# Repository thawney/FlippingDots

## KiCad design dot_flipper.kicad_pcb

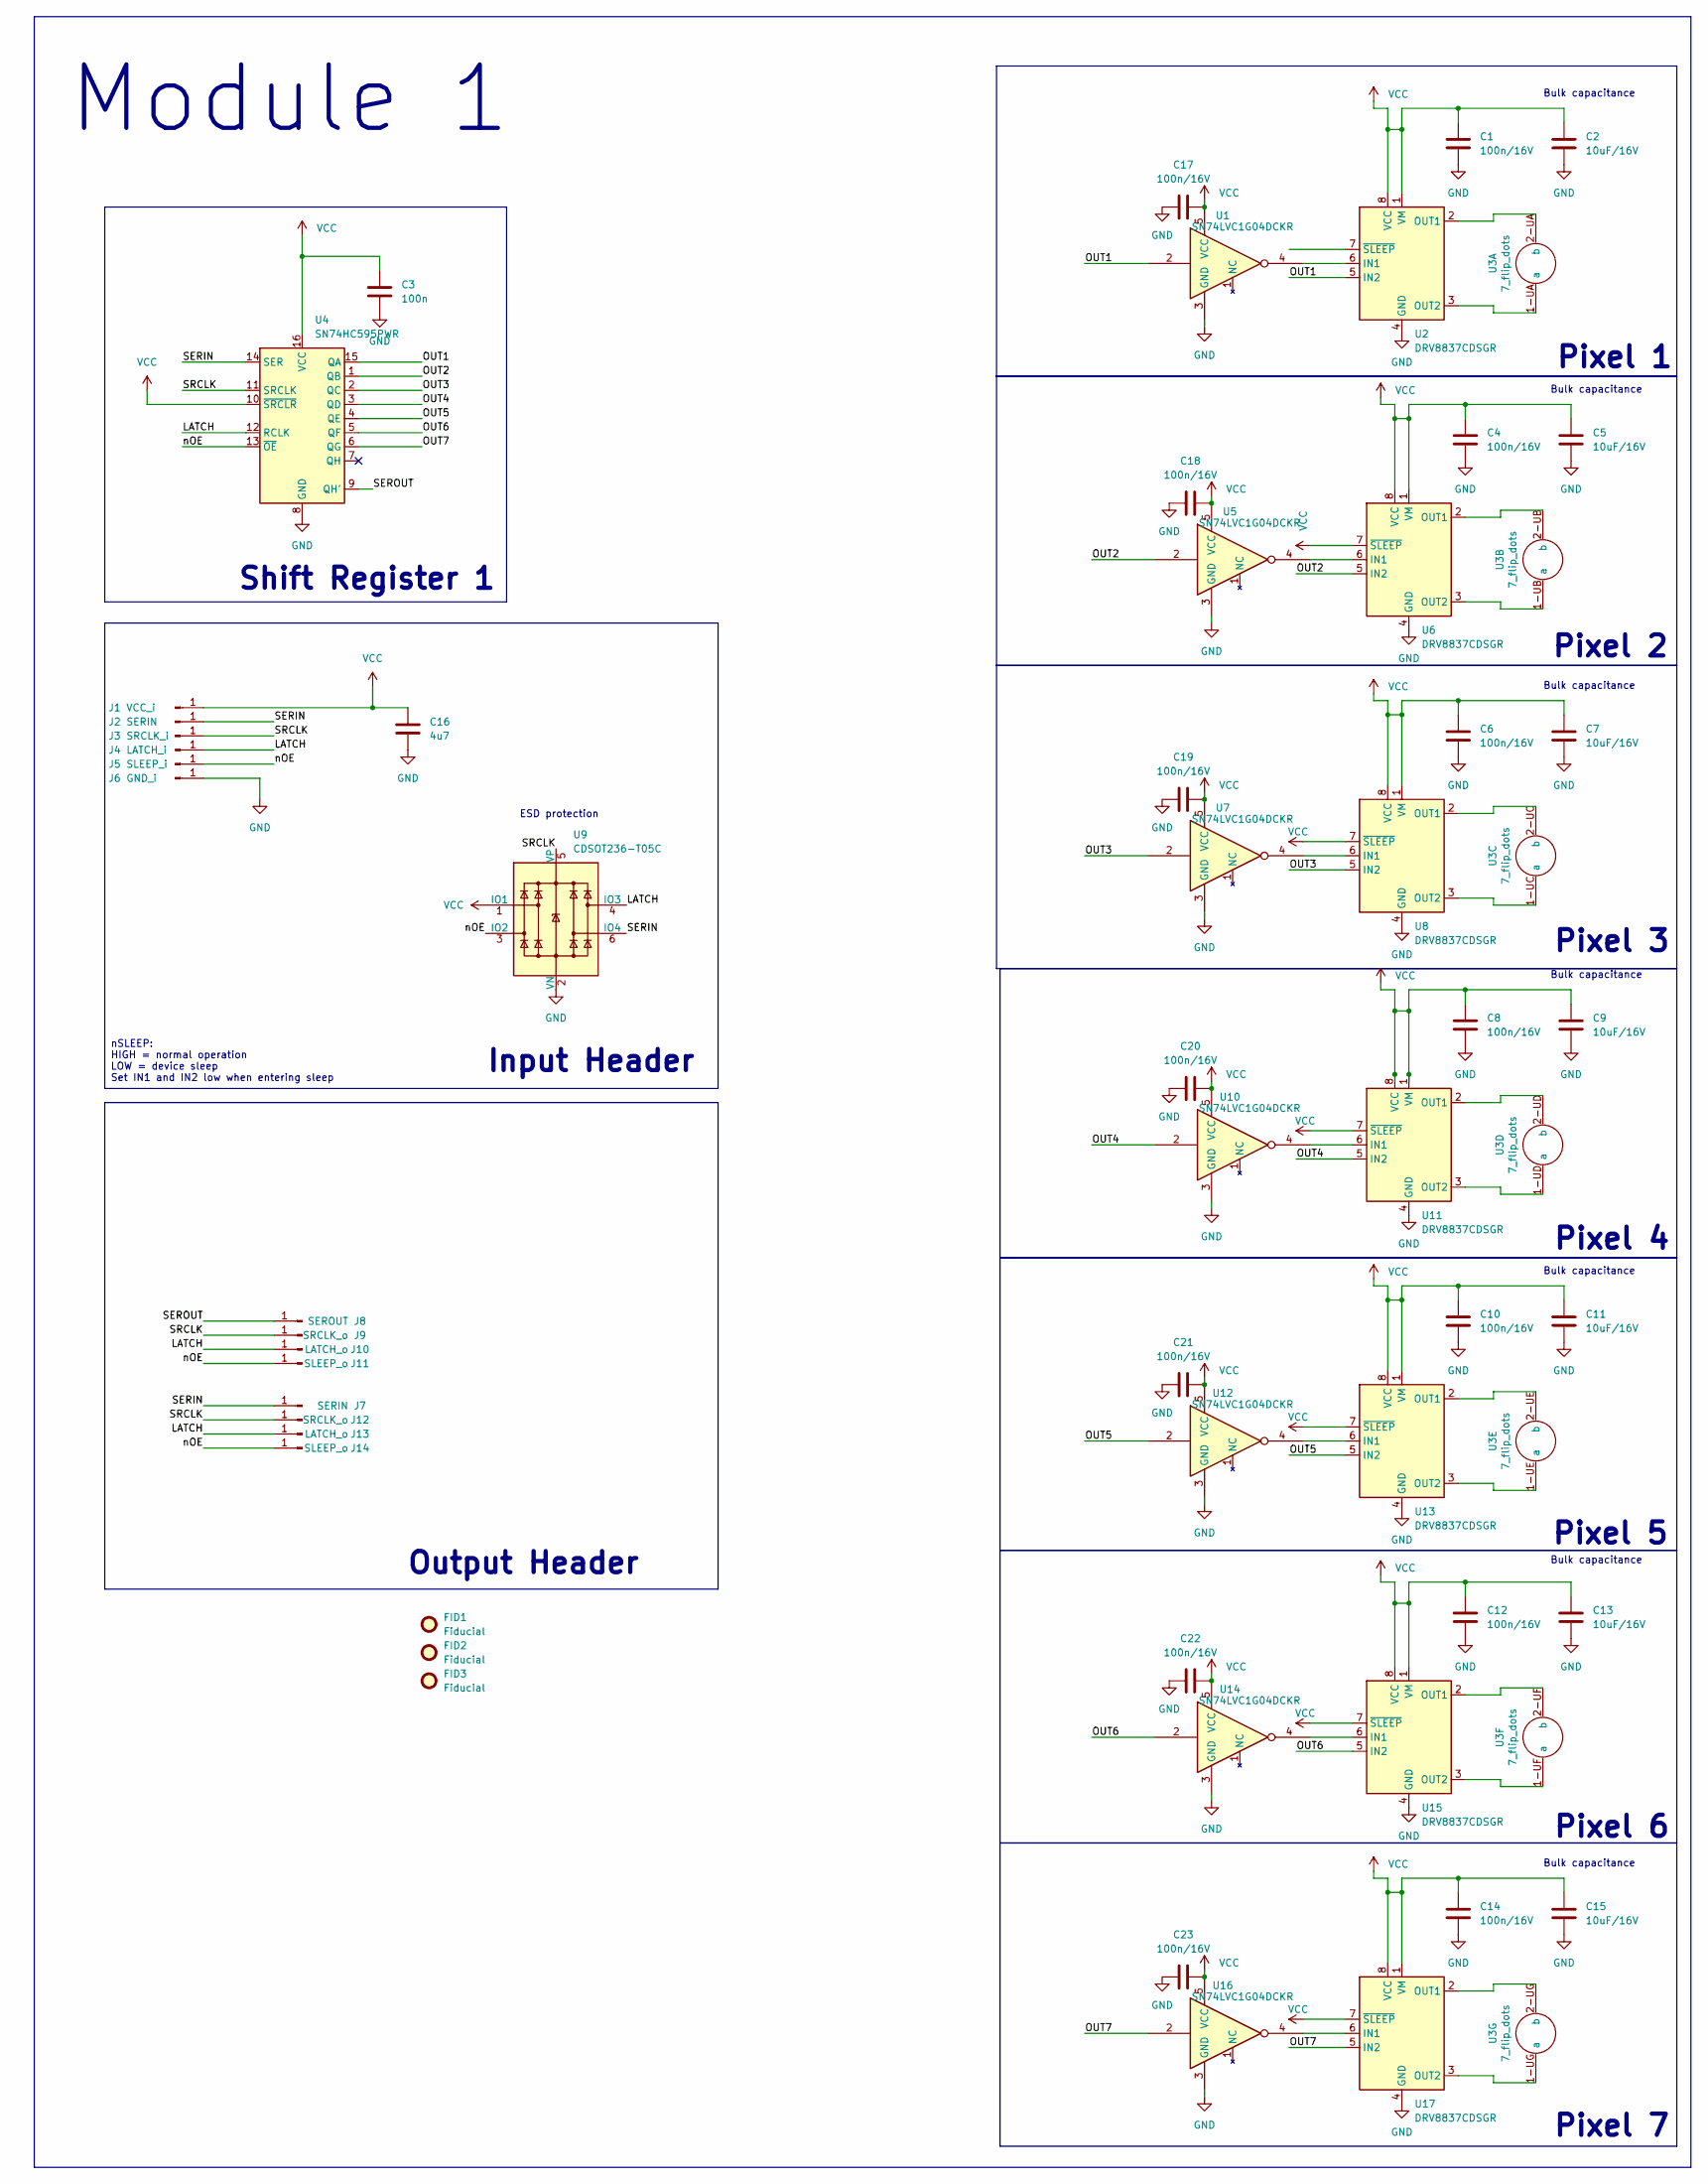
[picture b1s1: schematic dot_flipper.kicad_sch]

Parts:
C1, C4, C6, C8, C10, C12, C14, C17, C18, C19, C20, C21, C22, C23: 100n/16V; C_0603_1608Metric
C2, C5, C7, C9, C11, C13, C15: 10uF/16V; C_0603_1608Metric
C3: 100n; C_0603_1608Metric
C16: 4u7; C_0603_1608Metric
FID1, FID2, FID3: Fiducial; Fiducial_0.5mm_Mask1.5mm
J1: VCC_i; SolderWirePad_1x01_SMD_1x2mm
J2: SERIN; SolderWirePad_1x01_SMD_1x2mm
J3: SRCLK_i; SolderWirePad_1x01_SMD_1x2mm
J4: LATCH_i; SolderWirePad_1x01_SMD_1x2mm
J5: SLEEP_i; SolderWirePad_1x01_SMD_1x2mm
J6: GND_i; SolderWirePad_1x01_SMD_1x2mm
J7: SERIN; small_pad
J8: SEROUT; small_pad
J9, J12: SRCLK_o; small_pad
J10, J13: LATCH_o; small_pad
J11, J14: SLEEP_o; small_pad
U1, U5, U7, U10, U12, U14, U16: SN74LVC1G04DCKR; SOT-353_SC-70-5; LCSC C8207
U2, U6, U8, U11, U13, U15, U17: DRV8837CDSGR; WSON-8-1EP_2x2mm_P0.5mm_EP0.9x1.6mm; Digikey 296-47205-1-ND
U3: 7_flip_dots
U4: SN74HC595PWR; TSSOP-16_4.4x5mm_P0.65mm; Digikey 296-23258-1-ND
U9: CDSOT236-T05C; SOT-23-6; Digikey CDSOT236-T05CCT-ND

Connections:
/LATCH: J4.1, J10.1, J13.1, U4.12 (RCLK), U9.4 (IO3)
/OUT1: U1.2, U2.5 (IN2), U4.15 (QA)
/OUT2: U4.1 (QB), U5.2, U6.5 (IN2)
/OUT3: U4.2 (QC), U7.2, U8.5 (IN2)
/OUT4: U4.3 (QD), U10.2, U11.5 (IN2)
/OUT5: U4.4 (QE), U12.2, U13.5 (IN2)
/OUT6: U4.5 (QF), U14.2, U15.5 (IN2)
/OUT7: U4.6 (QG), U16.2, U17.5 (IN2)
/SERIN: J2.1, J7.1, U4.14 (SER), U9.6 (IO4)
/SEROUT: J8.1, U4.9 (QH')
/SRCLK: J3.1, J9.1, J12.1, U4.11 (SRCLK), U9.5 (VP)
/nOE: J5.1, J11.1, J14.1, U4.13 (~OE), U9.3 (IO2)
GND: C1.2, C2.2, C3.2, C4.2, C5.2, C6.2, C7.2, C8.2, C9.2, C10.2, C11.2, C12.2, C13.2, C14.2, C15.2, C16.2, C17.1, C18.1, C19.1, C20.1, C21.1, C22.1, C23.1, J6.1, U1.3 (GND), U2.4 (GND), U2.9 (GND), U4.8 (GND), U5.3 (GND), U6.4 (GND), U6.9 (GND), U7.3 (GND), U8.4 (GND), U8.9 (GND), U9.2 (VN), U10.3 (GND), U11.4 (GND), U11.9 (GND), U12.3 (GND), U13.4 (GND), U13.9 (GND), U14.3 (GND), U15.4 (GND), U15.9 (GND), U16.3 (GND), U17.4 (GND), U17.9 (GND)
unnamed: U1.4, U2.6 (IN1)
unnamed: U2.2 (OUT1), U3.2-UA (b)
unnamed: U2.3 (OUT2), U3.1-UA (a)
unnamed: U3.1-UB (a), U6.3 (OUT2)
unnamed: U3.2-UB (b), U6.2 (OUT1)
unnamed: U3.1-UC (a), U8.3 (OUT2)
unnamed: U3.2-UC (b), U8.2 (OUT1)
unnamed: U5.4, U6.6 (IN1)
unnamed: U7.4, U8.6 (IN1)
unnamed: U10.4, U11.6 (IN1)
unnamed: U3.2-UD (b), U11.2 (OUT1)
unnamed: U3.1-UD (a), U11.3 (OUT2)
unnamed: U12.4, U13.6 (IN1)
unnamed: U3.2-UE (b), U13.2 (OUT1)
unnamed: U3.1-UE (a), U13.3 (OUT2)
unnamed: U14.4, U15.6 (IN1)
unnamed: U3.2-UF (b), U15.2 (OUT1)
unnamed: U3.1-UF (a), U15.3 (OUT2)
unnamed: U16.4, U17.6 (IN1)
unnamed: U3.2-UG (b), U17.2 (OUT1)
unnamed: U3.1-UG (a), U17.3 (OUT2)
VCC: C1.1, C2.1, C3.1, C4.1, C5.1, C6.1, C7.1, C8.1, C9.1, C10.1, C11.1, C12.1, C13.1, C14.1, C15.1, C16.1, C17.2, C18.2, C19.2, C20.2, C21.2, C22.2, C23.2, J1.1, U1.5 (VCC), U2.1 (VM), U2.8 (VCC), U4.10 (~SRCLR), U4.16 (VCC), U5.5 (VCC), U6.1 (VM), U6.7 (~SLEEP), U6.8 (VCC), U7.5 (VCC), U8.1 (VM), U8.7 (~SLEEP), U8.8 (VCC), U9.1 (IO1), U10.5 (VCC), U11.1 (VM), U11.7 (~SLEEP), U11.8 (VCC), U12.5 (VCC), U13.1 (VM), U13.7 (~SLEEP), U13.8 (VCC), U14.5 (VCC), U15.1 (VM), U15.7 (~SLEEP), U15.8 (VCC), U16.5 (VCC), U17.1 (VM), U17.7 (~SLEEP), U17.8 (VCC)

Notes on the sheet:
Bulk capacitance
Output Header
Pixel 7
Pixel 6
ESD protection
Pixel 1
Module 1
Pixel 2
Input Header
Shift Register 1
Pixel 3
Pixel 5
Pixel 4
nSLEEP: HIGH = normal operation LOW = device sleep Set IN1 and IN2 low when entering sleep

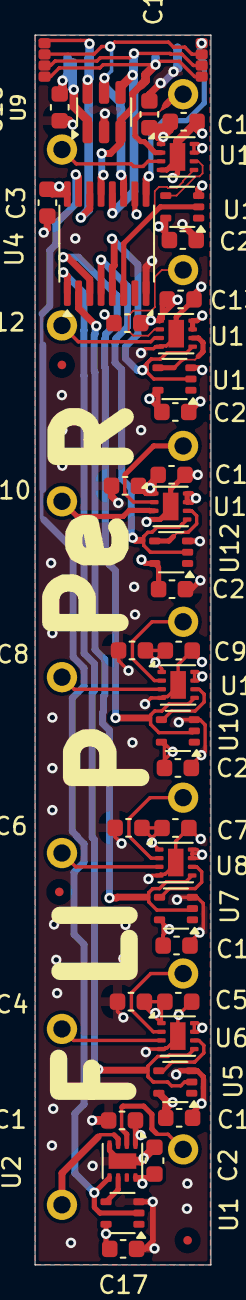
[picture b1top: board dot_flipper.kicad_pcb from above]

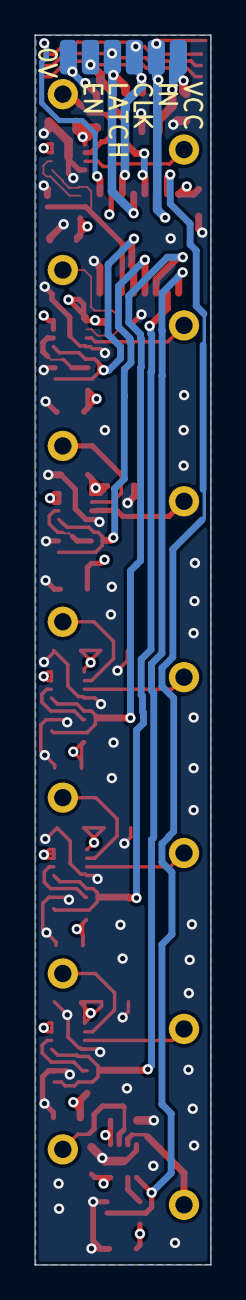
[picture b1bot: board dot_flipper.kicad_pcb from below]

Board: 4 copper layers, 10.2 x 71.0 mm, 57 parts (6 on the bottom side), 35 nets.

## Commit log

2025-01-24 landscaped schem
2025-01-24 Add DRV8837C
2025-01-24 added power schematic
2025-01-24 avoided silly names
2025-01-24 Updated with 2 H-bridges
2025-02-16 Single module schematic
2025-02-16 Rough component placement
    Slightly tweaked flipdot footprint to match my measurements and datasheet better
    Created board outline, interfaces.
    Rough component placement.
2025-02-25 Cost optimisation
    Removed one shift register by adding 7 signal inverters (now only need 7 shift register outputs instead of 14 to control 7 H-bridges)
2025-02-25 LCSC codes added
    Also broken out VM pin to input/output headers
2025-02-25 Power supply mod
    Connected VM to VCC to simplify operation and make PCB layout easier
2025-02-25 Started PCB layout
    Components in vaguely the correct area
2025-03-07 Update Mar 7 AM
    - Implemented bus architecture to transfer data to second column, and transport signals down to each pixel
    - simplified schematic more
    - routed first (most difficult) pixel
2025-03-07 Update Mar 7 PM
    All pixels routed
    7x7 variant created
